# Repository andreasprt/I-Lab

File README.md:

# I-Lab
Semua Program Mikro untuk I-Lab

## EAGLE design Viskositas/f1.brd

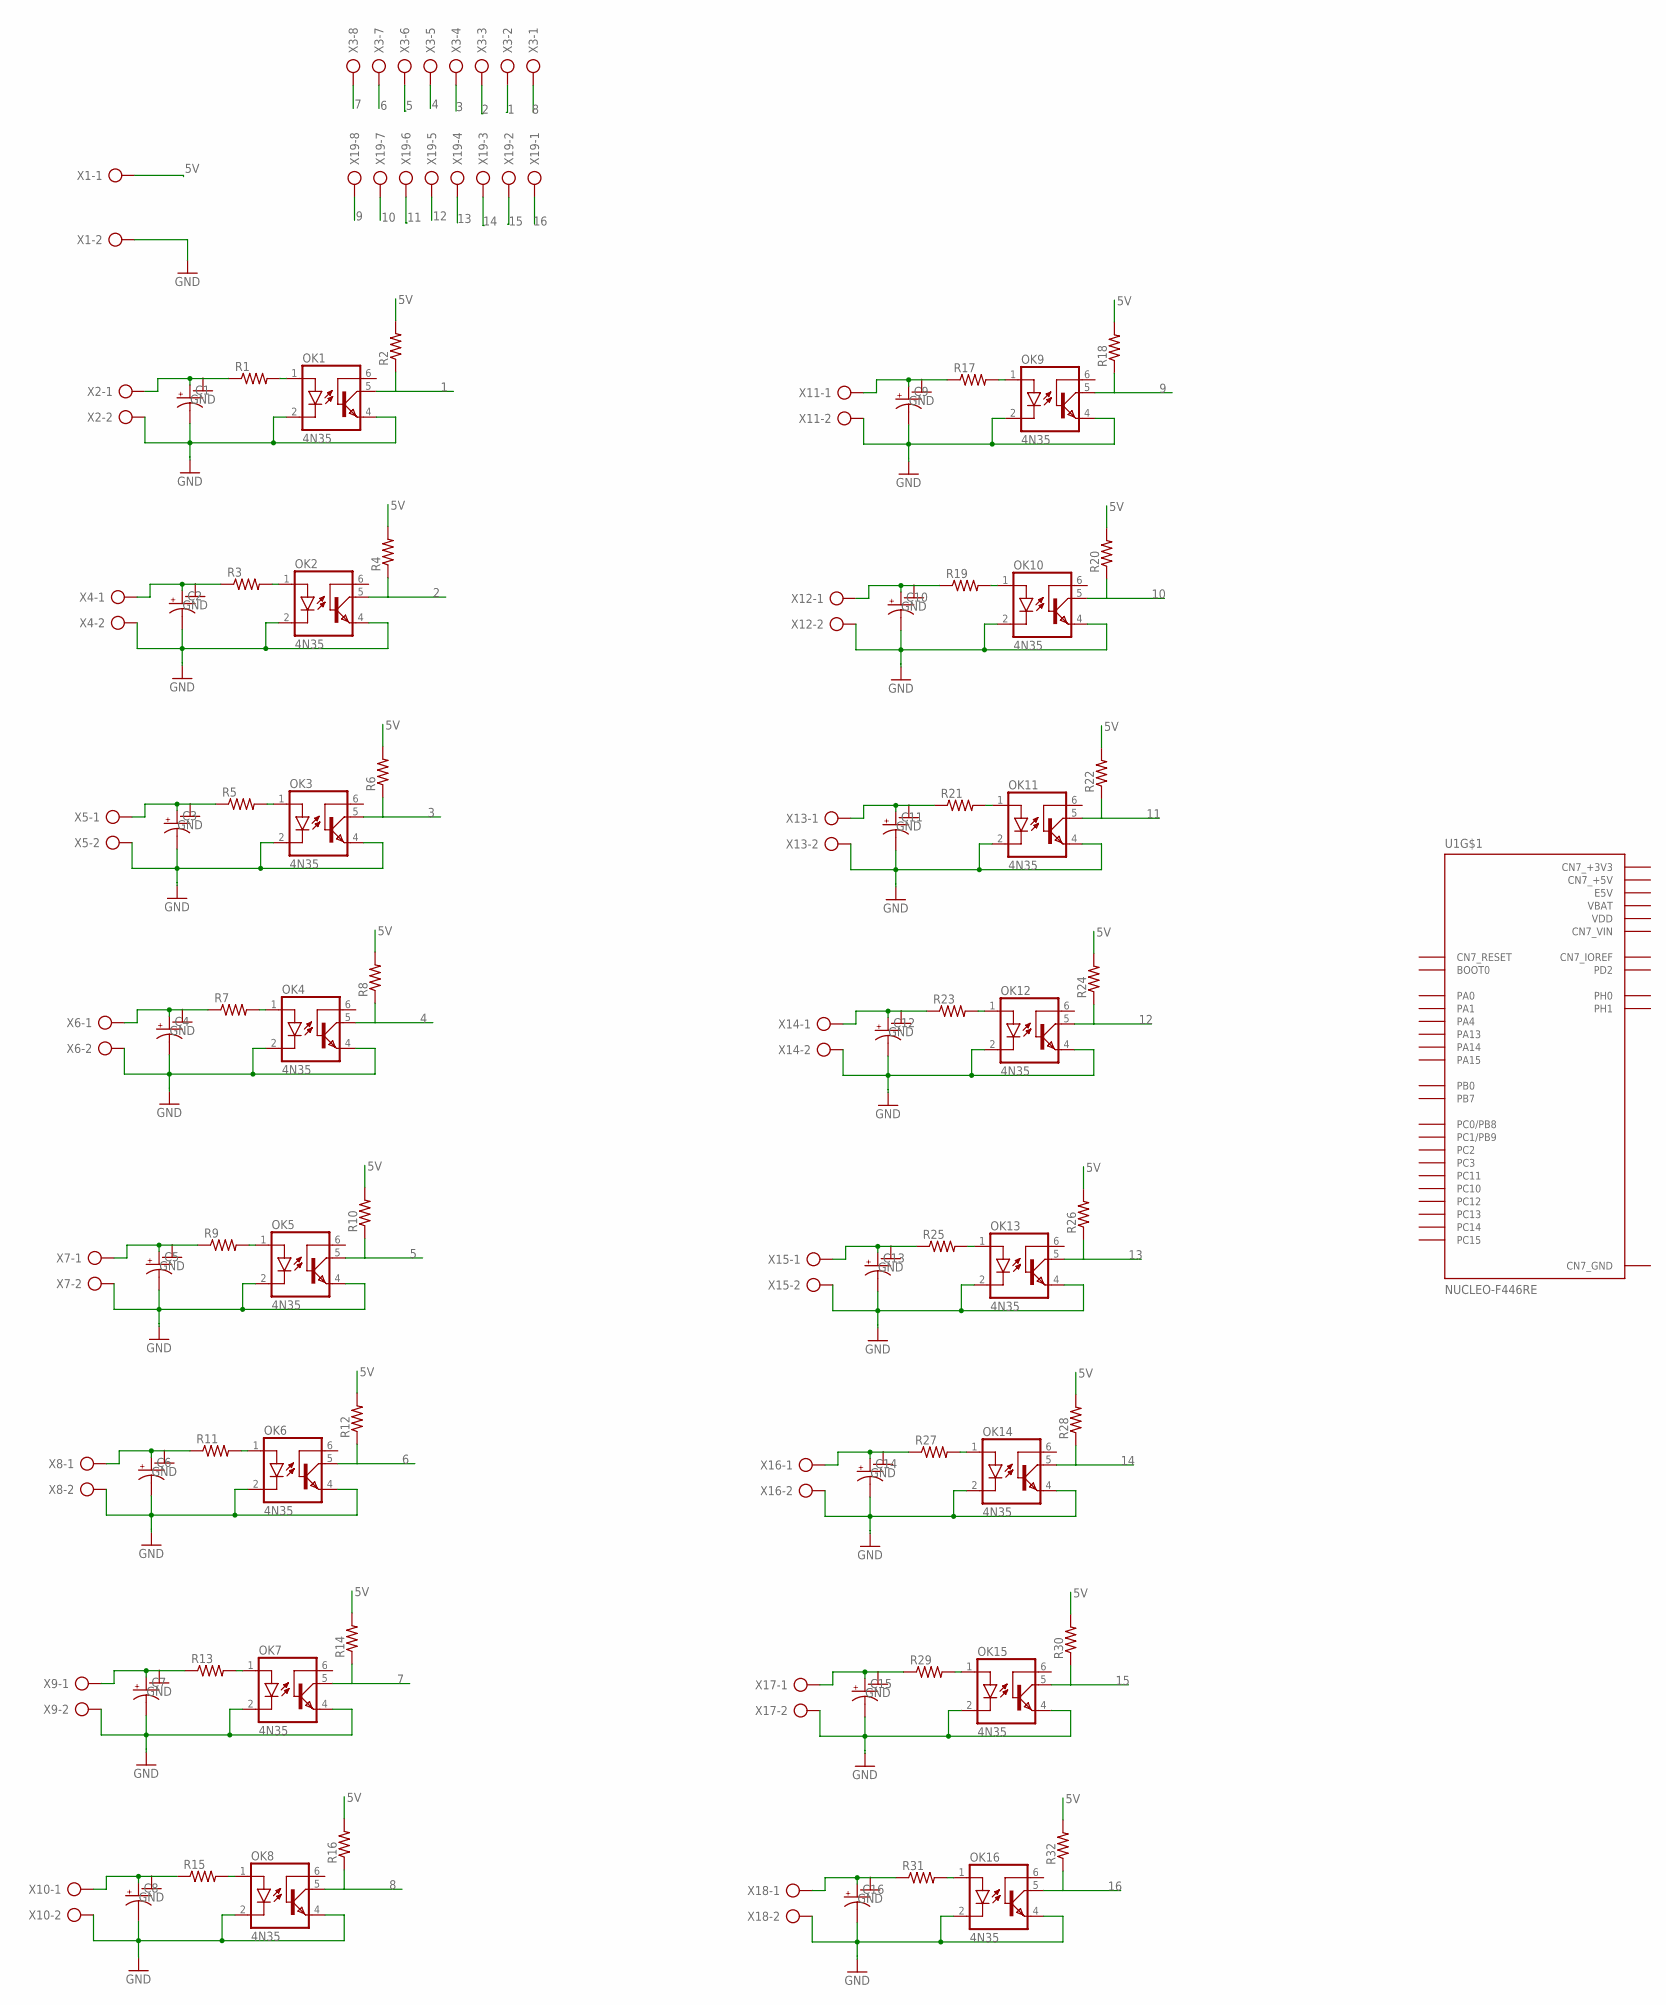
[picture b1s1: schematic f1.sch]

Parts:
C1, C2, C3, C4, C5, C6, C7, C9, C10, C11, C12, C13, C14, C15, C16: CPOL-USE3.5-10; E3,5-10
C8: CPOL-USE2.5-6; E2,5-6
OK1, OK2, OK3, OK4, OK5, OK6, OK7, OK8, OK9, OK10, OK11, OK12, OK13, OK14, OK15, OK16: 4N35; DIL06
R1, R2, R3, R4, R5, R6, R7, R8, R9, R10, R11, R12, R13, R14, R15, R16, R17, R18, R19, R20, R21, R22, R23, R24, R25, R26, R27, R28, R29, R30, R31, R32: R-US_0207/10; 0207/10
U1: NUCLEO-F446RE; MODULE_NUCLEO-F446RE
X1, X2, X4, X5, X6, X7, X8, X9, X10, X11, X12, X13, X14, X15, X16, X17, X18: AK300/2
X3, X19: AK300/8

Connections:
1: OK1.5 (COL), R2.1, X3.2
2: OK2.5 (COL), R4.1, X3.3
3: OK3.5 (COL), R6.1, X3.4
4: OK4.5 (COL), R8.1, X3.5
5: OK5.5 (COL), R10.1, X3.6
5V: R2.2, R4.2, R6.2, R8.2, R10.2, R12.2, R14.2, R16.2, R18.2, R20.2, R22.2, R24.2, R26.2, R28.2, R30.2, R32.2, X1.1
6: OK6.5 (COL), R12.1, X3.7
7: OK7.5 (COL), R14.1, X3.8
8: OK8.5 (COL), R16.1, X3.1
9: OK9.5 (COL), R18.1, X19.8
10: OK10.5 (COL), R20.1, X19.7
11: OK11.5 (COL), R22.1, X19.6
12: OK12.5 (COL), R24.1, X19.5
13: OK13.5 (COL), R26.1, X19.4
14: OK14.5 (COL), R28.1, X19.3
15: OK15.5 (COL), R30.1, X19.2
16: OK16.5 (COL), R32.1, X19.1
AGND: U1.CN10_32 (AGND)
AREF: U1.CN5_8 (AREF)
AVDD: U1.CN10_7 (AVDD)
CN5_GND: U1.CN5_7 (CN5_GND)
CN6_+3V3: U1.CN6_4 (CN6_+3V3)
CN6_+5V: U1.CN6_5 (CN6_+5V)
CN6_GND: U1.CN6_6 (CN6_GND), U1.CN6_7 (CN6_GND)
CN6_VIN: U1.CN6_8 (CN6_VIN)
CN7_+3V3: U1.CN7_16 (CN7_+3V3)
CN7_+5V: U1.CN7_18 (CN7_+5V)
CN7_GND: U1.CN7_8 (CN7_GND), U1.CN7_19 (CN7_GND), U1.CN7_20 (CN7_GND), U1.CN7_22 (CN7_GND)
CN7_VIN: U1.CN7_24 (CN7_VIN)
CN10_GND: U1.CN10_9 (CN10_GND), U1.CN10_20 (CN10_GND)
E5V: U1.CN7_6 (E5V)
GND: C1.-, C2.-, C3.-, C4.-, C5.-, C6.-, C7.-, C8.-, C9.-, C10.-, C11.-, C12.-, C13.-, C14.-, C15.-, C16.-, OK1.2 (C), OK1.4 (EMI), OK2.2 (C), OK2.4 (EMI), OK3.2 (C), OK3.4 (EMI), OK4.2 (C), OK4.4 (EMI), OK5.2 (C), OK5.4 (EMI), OK6.2 (C), OK6.4 (EMI), OK7.2 (C), OK7.4 (EMI), OK8.2 (C), OK8.4 (EMI), OK9.2 (C), OK9.4 (EMI), OK10.2 (C), OK10.4 (EMI), OK11.2 (C), OK11.4 (EMI), OK12.2 (C), OK12.4 (EMI), OK13.2 (C), OK13.4 (EMI), OK14.2 (C), OK14.4 (EMI), OK15.2 (C), OK15.4 (EMI), OK16.2 (C), OK16.4 (EMI), X1.2, X2.2, X4.2, X5.2, X6.2, X7.2, X8.2, X9.2, X10.2, X11.2, X12.2, X13.2, X14.2, X15.2, X16.2, X17.2, X18.2
unnamed: C2.+, R3.1, X4.1
unnamed: OK2.1 (A), R3.2
unnamed: C3.+, R5.1, X5.1
unnamed: C1.+, R1.1, X2.1
unnamed: OK1.1 (A), R1.2
unnamed: OK3.1 (A), R5.2
unnamed: C4.+, R7.1, X6.1
unnamed: OK4.1 (A), R7.2
unnamed: C5.+, R9.1, X7.1
unnamed: OK5.1 (A), R9.2
unnamed: C6.+, R11.1, X8.1
unnamed: OK6.1 (A), R11.2
unnamed: C7.+, R13.1, X9.1
unnamed: OK7.1 (A), R13.2
unnamed: C8.+, R15.1, X10.1
unnamed: OK8.1 (A), R15.2
unnamed: C9.+, R17.1, X11.1
unnamed: OK9.1 (A), R17.2
unnamed: C10.+, R19.1, X12.1
unnamed: OK10.1 (A), R19.2
unnamed: C11.+, R21.1, X13.1
unnamed: OK11.1 (A), R21.2
unnamed: C12.+, R23.1, X14.1
unnamed: OK12.1 (A), R23.2
unnamed: C13.+, R25.1, X15.1
unnamed: OK13.1 (A), R25.2
unnamed: C14.+, R27.1, X16.1
unnamed: OK14.1 (A), R27.2
unnamed: C15.+, R29.1, X17.1
unnamed: OK15.1 (A), R29.2
unnamed: C16.+, R31.1, X18.1
unnamed: OK16.1 (A), R31.2
U5V: U1.CN10_8 (U5V)
VBAT: U1.CN7_33 (VBAT)
VDD: U1.CN7_5 (VDD)

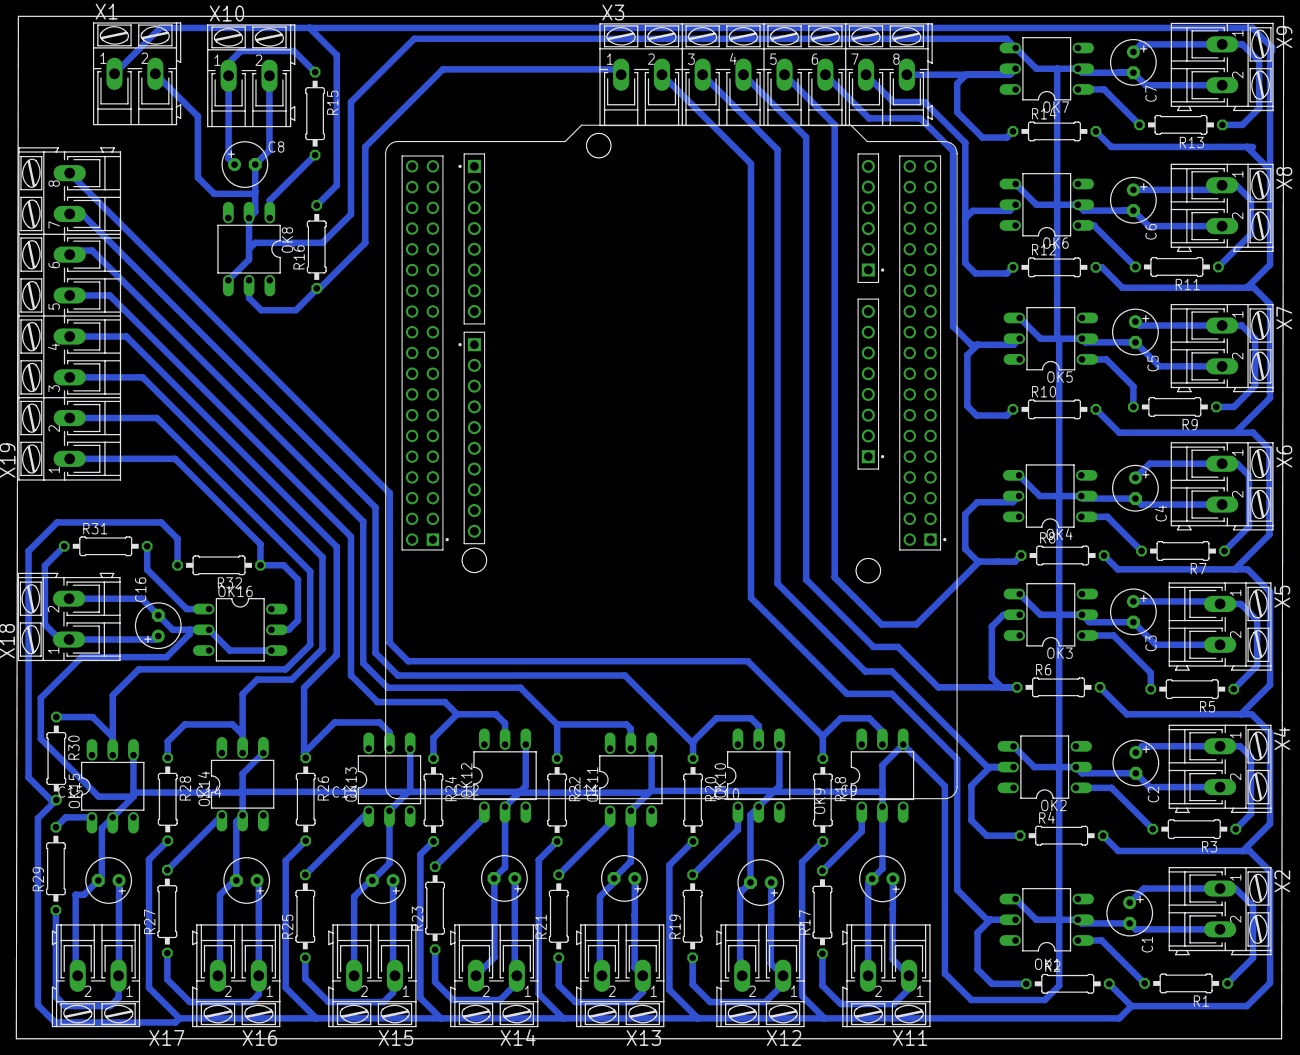
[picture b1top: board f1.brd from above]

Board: 2 copper layers, 155.2 x 125.2 mm, 84 parts (0 on the bottom side), 53 nets.

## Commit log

2021-08-25 membuat git
2021-08-25 menambah keterangan oada bandul Fisis
2021-08-27 Membuat Read.me
2021-09-02 update bandul fisis
2021-09-03 menambah program bandul matematis
2021-09-06 update B
2021-10-08 Update all
